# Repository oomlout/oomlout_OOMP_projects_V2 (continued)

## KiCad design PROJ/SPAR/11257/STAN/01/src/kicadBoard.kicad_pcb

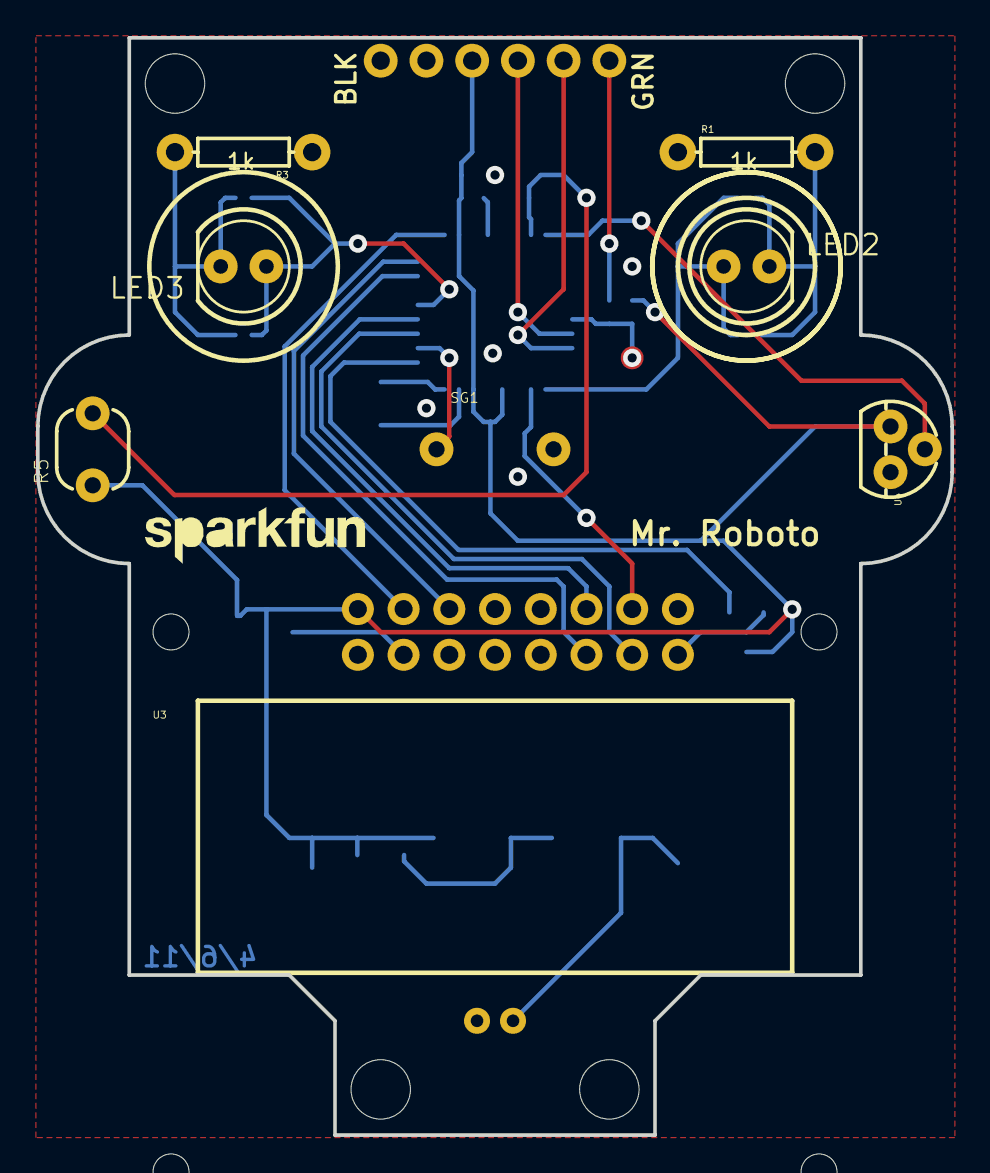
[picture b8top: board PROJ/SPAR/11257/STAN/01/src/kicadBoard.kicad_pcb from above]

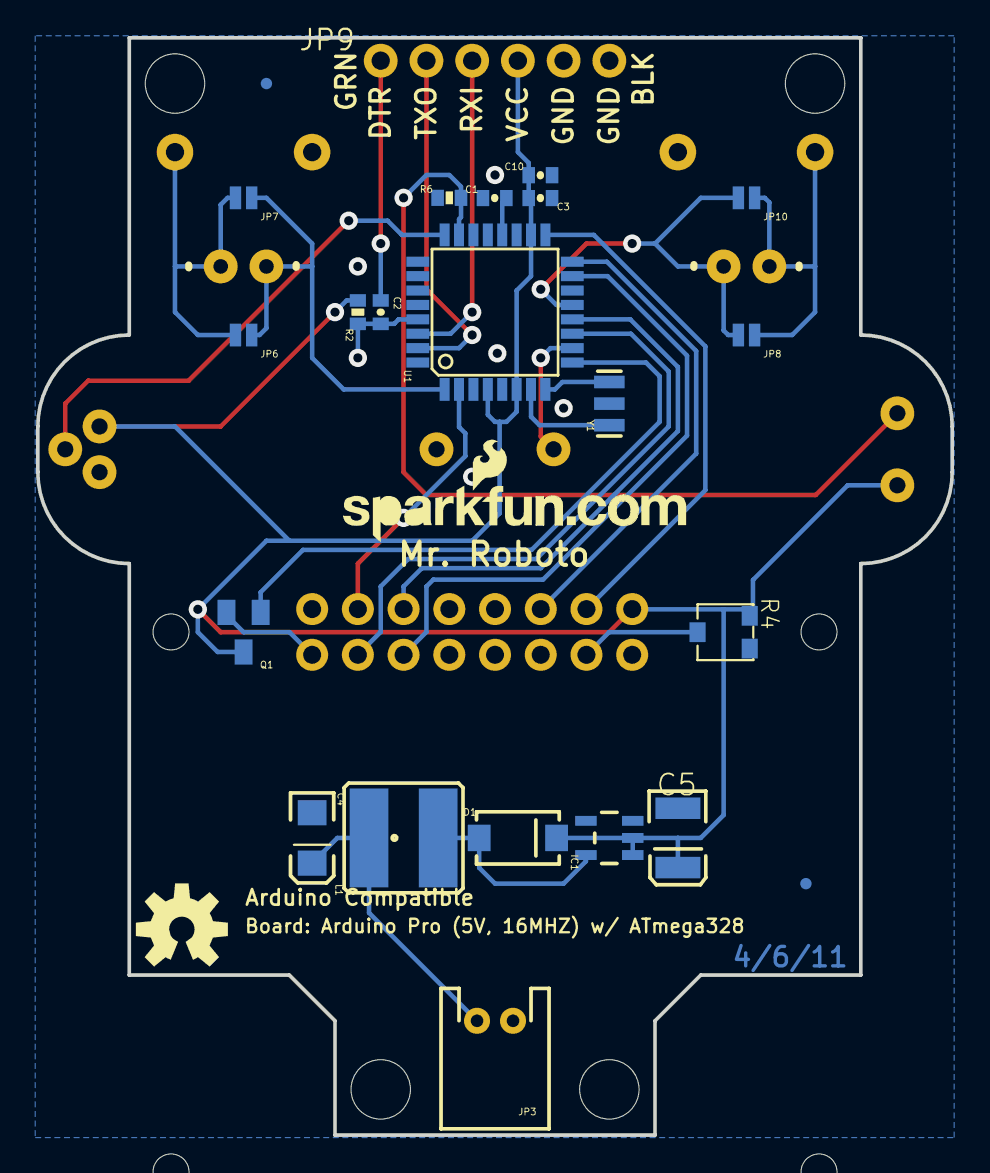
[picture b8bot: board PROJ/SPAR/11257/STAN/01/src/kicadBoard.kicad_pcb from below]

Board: 2 copper layers, 50.8 x 61.0 mm, 40 parts (25 on the bottom side), 27 nets.

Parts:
C1, C2, C3, C10: 0.1uF; 0402-CAP
C4: 10uF; EIA3216
C5: 68uF; EIA3528
D1: MBRA140; SMA-DIODE
IC1: NCP1402; SOT23-5
JP1, JP2, JP4, JP5: Long, Plastic; STAND-OFF
JP3: JST-PTH; JST-2-PTH-KIT
JP6, JP7, JP8, JP10: SJ_2S-NO-NS
JP9: Program; 1X06-KIT
JP11, JP12: FIDUCIAL1X2.5; FIDUCIAL-1X2.5
L1: 47uH; CR54
LED2, LED3: RED; LED5MM-KIT
Q1: SOT23
R1, R3: 1k; AXIAL-0.3-KIT
R2: 10K; 0402-RES
R4: TRIMPOT-2; TRIMPOT_TC33
R5: PHOTOCELLPTH; PHOTOCELL-KIT
R6: 10k; 0402-RES
SG1: BUZZER; BUZZER-12MM-NS-KIT
TP1: TP; PAD.03X.05
U1: ATmega328; TQFP32-08
U3: LCD-8x2; LCD-8X2-KIT
U4: TO-92-KIT
U$1: CREATIVE_COMMONS
U$2: OSHW-LOGOM; OSHW-LOGO-M
U$3: LOGO-SFENEW; SFE-NEW-WEBLOGO
U$11: LOGO-SFENW2; SFE-NEW-WEB
Y1: 16mhz; RESONATOR-SMD

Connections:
A0: R5.2, R6.2, U1.23
A1: U1.24, U4.2
AREF: C1.2, U1.20
D3: JP6.1, JP7.1, LED2.A, U1.1
D4: U1.2, U3.14
D5: Q1.1, U1.9
D6: SG1.-, U1.10
D7: U1.11, U3.13
D8: U1.12, U3.12
D9: JP8.2, JP10.2, LED3.A, U1.13
DTR: C2.1, JP9.1
GND: C1.1, C3.1, C4.C, C5.C, C10.2, IC1.4, JP3.1, JP9.5, JP9.6, R1.P$1, R3.P$1, R4.1, R6.1, SG1.+, U1.3, U1.5, U1.21, U3.1, U3.5, U3.7, U3.8, U3.9, U3.10, U3.16, U4.3, Y1.2
MISO: U1.16, U3.6
MOSI: U1.15, U3.11
unnamed: D1.A, IC1.5, L1.P$2
unnamed: Q1.2, U3.15
unnamed: U1.7, Y1.1
unnamed: JP8.1, JP10.1, LED3.K, R3.P$2
unnamed: U1.8, Y1.3
unnamed: JP6.2, JP7.2, LED2.K, R1.P$2
RESET: C2.2, R2.1, TP1.P$1, U1.29
RX-I: JP9.3, U1.30
SCK: U1.17, U3.4
TX-O: JP9.2, U1.31
V0: R4.2, U3.3
VCC: C3.2, C5.A, C10.1, D1.C, IC1.1, IC1.2, JP9.4, Q1.3, R2.2, R4.3, R5.1, U1.4, U1.6, U1.18, U3.2, U4.1
VIN: C4.A, JP3.2, L1.P$1
